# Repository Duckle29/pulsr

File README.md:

# Solenoid-shooter

***This doesn't seem to work all that well. More experimentation required.***

This tiny board is designed to handle quick pulses of current to a solenoid. It has a mosfet to trigger it, a capacitor for providing the pulse of current, and flyback diode, and an inrush limiting resistor. If fired at it's highest rate, the board should average out to ~100mA consumption

## Renders:

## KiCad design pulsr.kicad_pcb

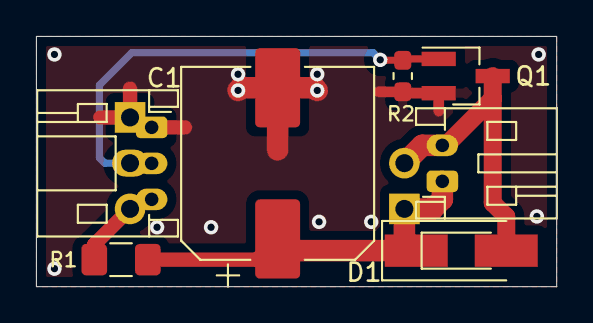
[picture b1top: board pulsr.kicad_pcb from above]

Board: 2 copper layers, 28.9 x 13.9 mm, 10 parts (0 on the bottom side), 5 nets.

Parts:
C1: FC0H473ZFTBR24; CP_Elec_10x10.5
D1: 1N4007L; D_SMA_Handsoldering
D1#2: 1N4007L; D_SOD-123F
J1: JST_PH; JST_PH_S3B-PH-K_1x03_P2.00mm_Horizontal
J2: 0.1" header; PinHeader_1x02_P2.54mm_Vertical
J2#2: 0.1" header; PinHeader_1x03_P2.54mm_Vertical
L1: solenoid; JST_PH_S2B-PH-K_1x02_P2.00mm_Horizontal
Q1: FDN339AN; SOT-23_Handsoldering
R1: 22R; R_1206_3216Metric_Pad1.42x1.75mm_HandSolder
R2: 10k; R_0603_1608Metric_Pad1.05x0.95mm_HandSolder

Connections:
+5V: J1.3, J2#2.3, R1.2
/FIRE!: J1.2, J2#2.2, Q1.1, R2.2
GND: C1.2, J1.1, J2#2.1, Q1.2, R2.1
unnamed: C1.1, D1.1, D1#2.1, J2.1, L1.1, R1.1
unnamed: D1.2, D1#2.2, J2.2, L1.2, Q1.3

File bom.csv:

"Id";"Designator";"Package";"Quantity";"Designation";"Supplier and ref";
1;"C1";"CP_Elec_6.3x5.4";1;"220uF";;;
2;"D1";"D_SOD-123F";1;"1N4007L";;;
3;"J1";"JST_PH_S3B-PH-K_1x03_P2.00mm_Horizontal";1;"JST_PH";;;
4;"L1";"JST_PH_S2B-PH-K_1x02_P2.00mm_Horizontal";1;"solenoid";;;
5;"Q1";"SOT-23_Handsoldering";1;"FDN339AN";;;
6;"J2";"PinHeader_1x03_P2.54mm_Vertical";1;"0.1" header";;;
7;"R1";"R_1206_3216Metric_Pad1.42x1.75mm_HandSolder";1;"22R";;;

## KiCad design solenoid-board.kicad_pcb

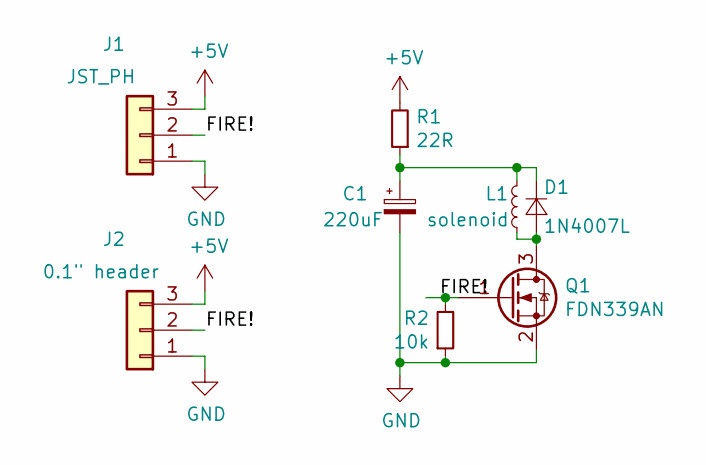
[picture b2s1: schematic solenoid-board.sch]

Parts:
C1: 220uF; CP_Elec_6.3x5.4
D1: 1N4007L; D_SOD-123F
J1: JST_PH; JST_PH_S3B-PH-K_1x03_P2.00mm_Horizontal
J2: 0.1\" header; PinHeader_1x03_P2.54mm_Vertical
L1: solenoid; JST_PH_S2B-PH-K_1x02_P2.00mm_Horizontal
Q1: FDN339AN; SOT-23_Handsoldering
R1: 22R; R_1206_3216Metric_Pad1.42x1.75mm_HandSolder
R2: 10k; R_0603_1608Metric_Pad1.05x0.95mm_HandSolder

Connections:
+5V: J1.3, J2.3, R1.2
/FIRE!: J1.2, J2.2, Q1.1 (G), R2.2
GND: C1.2, J1.1, J2.1, Q1.2 (S), R2.1
unnamed: C1.1, D1.1 (K), L1.1, R1.1
unnamed: D1.2 (A), L1.2, Q1.3 (D)

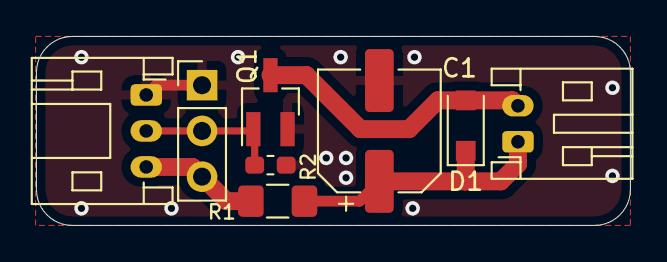
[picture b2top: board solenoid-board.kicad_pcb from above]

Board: 2 copper layers, 33.0 x 10.5 mm, 8 parts (0 on the bottom side), 5 nets.

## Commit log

2019-09-09 Create LICENSE
2019-09-09 Saved and quit kicad
2019-09-09 Added pdf of schematic
2019-09-09 Added BOM and position file
2019-09-09 Added v-cut panel version
2019-09-09 Added zip
2019-09-24 Fixed mosfet pinout and added gate pulldown
2019-09-24 updated panelized design
2019-09-26 Updated renders
2019-10-20 Renamed files and updated panelized
2019-10-20 fixed overwritten files
2019-11-08 Modified design to fit 47mF super-cap
